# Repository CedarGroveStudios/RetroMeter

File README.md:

# RetroMeter
A breakout and FeatherWing PCB family with CircuitPython code that converts a +/-10V CV signal to a current level compatible with a retro analog ammeter. USB or 3 to 6V battery powered (no internal battery charger). From the collaborative project with John Park’s Workshop.

The Retro CV Meter breakout and FeatherWing board accepts a -10 to +10 volt signal and through an analog op-amp, translates it into a +3.3 to 0 volt signal connected to the Adafruit Trinket M0 or Feather's A1 analog input pin. The A0~ DAC output pin provides current output through a 2K-ohm resistor to the analog meter connection. The maximum DAC value (65535) produces 1.5mA to the attached meter.

The CircuitPython code reads the input voltage and adjusts the DAC output for the scale for the meter. The ``inertia_move`` helper integrates the incoming signal then sends the scaled and smoothed voltage to the on-board meter resistor to convert the voltage to current compabile with the analog meter. The integration routine protects the meter movement from sudden voltage changes.

The most recent version of the code reads a meter scale input from a potentiometer attached to pin A2. The D3 pin provides a PWM output proportional to the absolute value of the input voltage within the specified range.

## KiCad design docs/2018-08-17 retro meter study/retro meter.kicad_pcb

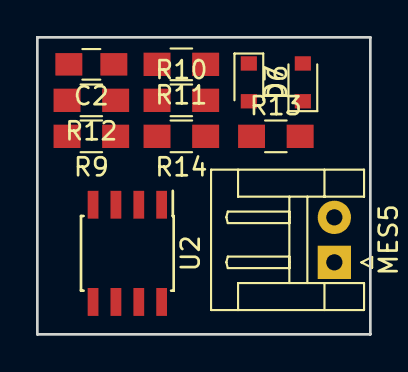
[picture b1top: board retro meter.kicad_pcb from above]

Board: 2 copper layers, 18.5 x 16.5 mm, 11 parts (0 on the bottom side), 7 nets, no tracks yet.

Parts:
C2: 0.1uF; C_0805_HandSoldering
D6, D7: DIODE; D_0805
MES5: 100uA; JST_EH_S02B-EH_02x2.50mm_Angled
R9: 600K; R_0805_HandSoldering
R10, R11, R12: 100K; R_0805_HandSoldering
R13: 33K; R_0805_HandSoldering
R14: 10K; R_0805_HandSoldering
U2: TL072; SOIC-8_3.9x4.9mm_Pitch1.27mm

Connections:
+3V3: D6.1, R10.2
GND: D7.2, MES5.1, R11.1
unnamed: C2.1, R12.1, R14.2, U2.1
unnamed: C2.2, R9.1, R12.2, U2.2
unnamed: MES5.2, R13.1
unnamed: R10.1, R11.2, U2.3
Trinket_A0: D6.2, D7.1, R14.1

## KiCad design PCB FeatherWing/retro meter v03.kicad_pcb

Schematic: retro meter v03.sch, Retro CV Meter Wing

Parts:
C1: 10uF; C_0805
C2: 0.1uF; C_0805
C3: 0.01uF; C_0805
D1: GRN LED; LED_0805_HandSoldering
J1: CV_INPUT; Pin_Header_Straight_1x02_Pitch2.54mm
J2: POWER_SWITCH; Pin_Header_Straight_1x02_Pitch2.54mm
J3: RANGE_SEL; Pin_Header_Straight_1x03_Pitch2.54mm
J4: METER_OUTPUT; Pin_Header_Straight_1x02_Pitch2.54mm
J5: LED1; Pin_Header_Straight_1x02_Pitch2.54mm
J6: LED2; Pin_Header_Straight_1x02_Pitch2.54mm
J7: LED3; Pin_Header_Straight_1x02_Pitch2.54mm
M1: Feather_M4_Express; Adafruit_Feather_M4_Express_bare
MES1: 1.6mA
P1: PKMCS0909E4000-R1
R1: 133K; R_0805
R2, R3, R5, R14, R15: 100K; R_0805
R4: 600K; R_0805
R6, R7: 10K; R_0805
R8: 2K; R_0805_HandSoldering
R9, R10, R11: 220; R_0805_HandSoldering
R12: 100M; R_Axial_DIN0309_L9.0mm_D3.2mm_P2.54mm_Vertical
R13: 470; R_0805
RV1: RANGE_SELECT
U1: TLV2462; SOIC-8_3.9x4.9mm_Pitch1.27mm
U2, U3, U4: 74HCT1G125; TSOP-5_1.65x3.05mm_Pitch0.95mm_hand_solder

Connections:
+3V3: C1.1, C2.1, J3.2, M1.2, R1.2, R13.2, R14.2, U1.8 (V+), U2.6, U3.6, U4.6
/-EN: J2.1, M1.18
/A0~~: M1.5, R8.2, R12.2
/A2: M1.7, R7.1, U1.7
/A3: J3.1, M1.8
/D5: M1.26, U2.2
/D6: M1.25, U3.2
/D9: M1.24, U4.2
/D10: M1.23, P1.1
/Vref1: R1.1, R2.2, U1.3 (+)
/Vref2: R14.1, R15.2, U1.5 (+)
GND: C1.2, C2.2, D1.1, J1.2, J2.2, J3.3, J4.2, J5.2, J6.2, J7.2, M1.4, P1.2, R2.1, R3.1, R15.1, U1.4 (V-), U2.1, U2.3, U3.1, U3.3, U4.1, U4.3
unnamed: C3.1, R5.1, R6.2, U1.1
unnamed: C3.2, R4.1, R5.2, U1.2 (-)
unnamed: D1.2, R13.1
unnamed: J1.1, R3.2, R4.2
unnamed: J4.1, R8.1, R12.1
unnamed: J5.1, R9.1
unnamed: J6.1, R10.1
unnamed: J7.1, R11.1
unnamed: R6.1, R7.2, U1.6 (-)
unnamed: R9.2, U2.4
unnamed: R10.2, U3.4
unnamed: R11.2, U4.4

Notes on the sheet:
Meter output scaling: Adjust R8 for meter full-scale value R8 = 3.3V / 1.5mA = 2.2K ohms
voltage sum stage CV gain = -0.1667 Vref gain = +1.1667
-10V to +10V
+1.416V
input -> output -10v 0v 0v +1.65v +10v +3.3v
power management
microcontroller
desired CV Gain = Voutpk_pk / Vinpk_pk desired CV Gain = 3.3v / 20v = 0.165 actual CV Gain = R5 / R4 = 0.1667 Vref1 = ( 3.3v / 2 ) / [ 1+ ( 100K / 600K ) ] Vref1 = 1.65v / 1.1667 Vref1 = 1.414v Actual Vref1 = [ 3.3v / ( 100K + 133K ) ] * 100K Actual Vref1 = 1.416v C1 = rate / ( 2pi * R5) 0.01uF = 0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
1.0 gain inverter stage
Standalone Analog Mode: Provide power to 3V pin using https://www.adafruit.com/product/2745 Jumper pin A0 to pin A2
(through-hole)
Vf=2.1v @ 5mA
Vf=2.1v @ 10mA
Feather Pin Usage: 3V: powers all internal components and external LEDs GND: common ground for everything A0~: digital-to-analog (DAC) output to series meter resistor A2: analog input from op-amp input signal processing stage A3: analog input from range selection potentiometer D5: digital output to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
range select input
piezo speaker
buffered LED outputs
analog input signal processing stage
+1.650V

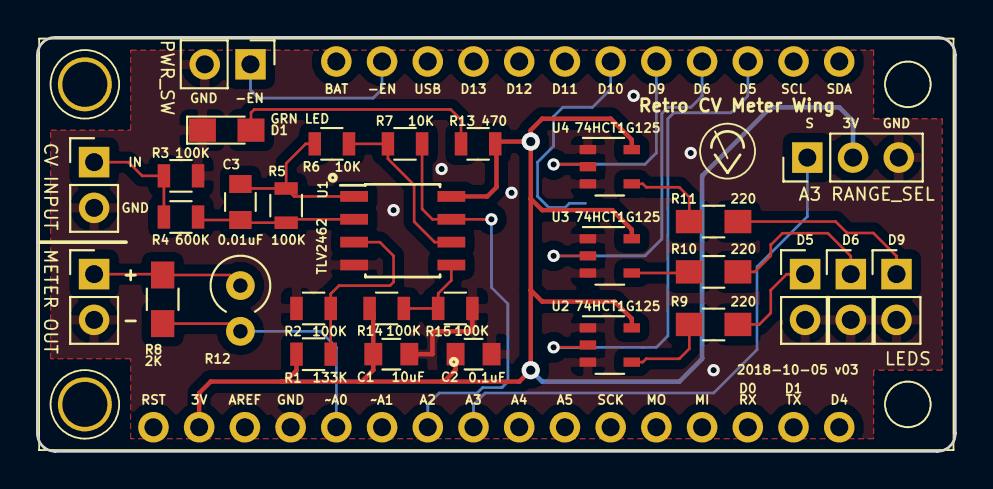
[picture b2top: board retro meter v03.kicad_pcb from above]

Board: 2 copper layers, 51.0 x 23.0 mm, 32 parts (1 on the bottom side), 24 nets.

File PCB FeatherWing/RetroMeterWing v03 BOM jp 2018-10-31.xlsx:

| Retro CV Meter Wing v03
 |  | Designation | Qty | JP Care Pkg | Value | Description | DigiKey | Adafruit
 |  | C1 | 1 |  | 10uF | SMT 0805 capacitor, ceramic, 16v | 490-5519-1-ND‎
 |  | C2 | 1 |  | 0.1uF | SMT 0805 capacitor, ceramic, 16v | 399-11163-1‎
 |  | C3 | 1 | 2 | 0.01uF | SMT 0805 capacitor, ceramic, 16v | 311-3161-1-ND
 |  | D1 | 1 | 2 | Green | SMT 0805 LED, GRN | 754-1651-1-ND
 |  | J1-J7 |  |  |  | Various male pin headers, 0.1" spacing |  | PID #392
 |  | M1 |  |  |  | Feather male pin or socket headers, 0.1" spacing
 |  | P1 | 1 | 2 | PKMCS0909E4000-1 | SMT piezo speaker | 490-9647-1-ND
 |  | R1 | 1 |  | 133K ohms | SMT 0805 resistor 0.1%, 1/8W | YAG1777CT-ND
 |  | R2, R3, R5, R14, R15 | 5 |  | 100K ohms | SMT 0805 resistor, 1% 1/8W | P100KCCT-ND‎
 |  | R5 | 1 |  | 600K ohms (604K) | SMT 0805 resistor, 1% 1/8W | P604KCCT-ND
 |  | R6, R7 | 2 |  | 10K ohms | SMT 0805 resistor, 1% 1/8W | P10.0KCCT-ND‎
 |  | R8 (or R12) | 1 |  | 2K ohms (matched to meter) | SMT 0805 resistor, 1% 1/8W (or through-hole) | YAG1322CT-ND
 |  | R9, R10, R11 | 3 | 6 | 220 ohms | SMT 0805 resistor, 1% 1/8W | YAG3711CT-ND
 |  | R13 | 1 | 2 | 470 ohms | SMT 0805 resistor, 1% 1/8W | YAG3733CT-ND
 |  | RV1 | 1 |  | 10K ohms | Potentiometer
 |  | U1 | 1 | 2 | TLV2462 | Dual SOIC-8 op-amp, single supply 2v to 6v | 296-2434-1-ND
 |  | U2, U3, U4 | 3 | 6 | 74HCT1G125 | SMT TSOP-5 tri-state buffer | ‎1727-6054-1-ND‎

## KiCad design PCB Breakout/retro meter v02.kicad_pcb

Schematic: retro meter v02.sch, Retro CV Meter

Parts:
C1, C3: 0.1uF; C_0805_HandSoldering
C2: 10uF
J1: CV_INPUT; Pin_Header_Straight_1x02_Pitch2.54mm
J2: POWER_SWITCH; Pin_Header_Straight_1x02_Pitch2.54mm
J3: LIPO_BATTERY; JST_PH_S2B-PH-SM4-TB_02x2.00mm_Angled
J4: D0/A2; Pin_Header_Straight_1x03_Pitch2.54mm
J5: D3/A3; Pin_Header_Straight_1x03_Pitch2.54mm
J6: D4/A4; Pin_Header_Straight_1x03_Pitch2.54mm
J7: METER_OUTPUT; Pin_Header_Straight_1x02_Pitch2.54mm
MES1: 1.6mA
R2, R4, R6, R8: 100K; R_0805_HandSoldering
R3: 133K; R_0805_HandSoldering
R5: 600K; R_0805_HandSoldering
R9: 2K; R_0805_HandSoldering
U1: TLV2461; SOIC-8_3.9x4.9mm_Pitch1.27mm
U2: Trinket_M0; Trinket_M0_no_holes

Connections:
+3V3: C2.1, C3.1, J4.2, J5.2, J6.2, R3.2, R8.2, U1.7 (V+), U2.6
+BATT: J2.1, U2.1
/A0~~: R9.2, U2.8
/A1: C1.1, R6.1, U1.6, U2.7
/D0: J4.1, U2.9
/D3: J5.1, U2.4
/D4: J6.1, U2.3
/Vref: R3.1, R4.2, U1.3 (+)
GND: C2.2, C3.2, J1.2, J3.2, J4.3, J5.3, J6.3, J7.2, R2.1, R4.1, U1.4 (V-), U2.2
unnamed: C1.2, R5.1, R6.2, U1.2 (-)
unnamed: J1.1, R2.2, R5.2
unnamed: J2.2, J3.1
unnamed: J7.1, R9.1
unnamed: R8.1, U2.5

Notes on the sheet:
adjust R8 for meter full-scale value R8 = 3.3V / 1.6mA = 2K ohms
0.167 gain inverter stage
Span: adjust R6 Zero: adjust ratio of R3 and R4
C1 = rate / ( 2pi * R5) 0.1uF = 0.038sec / (6.28 * 60K)
-10V to +10V
+1.42V
input -> output -10v +3.3v 0v +1.65v +10v 0v
DAC output scaling
GPIO
power management
microcontroller
Vref = Rf ( Vinpk_pk / ( 2 ( Rf + Rin ) ) ) Vref = 10K ( 20v / ( 2 (10K + 60K ) ) ) Vref = 1.42v
Gain = Voutpk_pk / Vinpk_pk Gain = 3.3v / 20v = 0.165

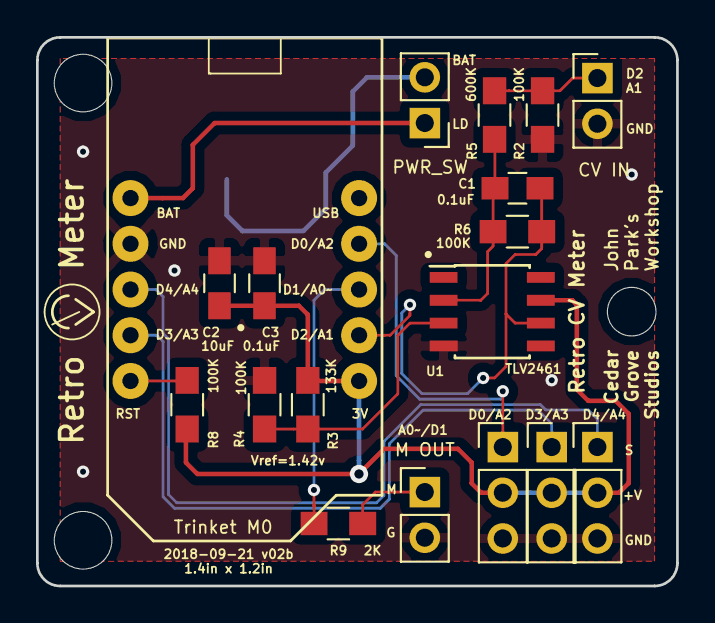
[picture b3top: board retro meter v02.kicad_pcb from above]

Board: 2 copper layers, 35.6 x 30.5 mm, 19 parts (1 on the bottom side), 14 nets.

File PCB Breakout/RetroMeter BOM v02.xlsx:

| Retro CV Meter
 |  | Designation | Qty | Value | Description | DigiKey | Adafruit
 |  | R5 | 1 | 600K ohms (604K) | SMT 0805 resistor, 1% 1/8W | 311-604KCRCT-ND‎
 |  | R2, R4, R6, R8 | 4 | 100K ohms | SMT 0805 resistor, 1% 1/8W | P100KCCT-ND‎
 |  | R3 | 1 | 133K ohms | SMT 0805 resistor, 1% 1/8W | P133KCCT-ND‎
 |  | R9 | 1 | 2K ohms (matched to meter) | SMT 0805 resistor, 1% 1/8W | YAG1322CT-ND
 |  | C1, C3 | 2 | 0.1uF | SMT 0805 capacitor, ceramic, 16v | 399-11163-1‎
 |  | C2 | 1 | 10uF | SMT 0805 capacitor, ceramic, 16v | 490-5519-1-ND‎
 |  | U1 | 1 | TLV2461 | SOIC-8 op-amp, single supply 2v to 6v | 296-2434-1-ND‎
 |  | U2 | 1 | Trinket M0 | microcontroller sub-module | 1528-2361-ND‎ | PID #3500
 |  | J3 | 1 | JST_PH_S2B-PH-SM4-TB_02x2.00mm_Angled | 2-pin SMD JST connector |  | PID #1769
 |  | J1-J7 |  |  | Male pin headers, 0.1" spacing |  | PID #392

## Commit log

2018-08-21 jst connector
    added battery jst connector
2018-09-01 Initial code
2018-09-01 Added external LED support
    Polarity indicators added to GPIO pins. D0=1 when signal is negative, D2=1 when signal is near zero, D4=1 when signal is positive.
2018-09-04 updated
    More fully annotated. Changed default parameters. Improved (slowed) initial meter needle positioning.
2018-09-04 no frills version
    A no frills version of the code without signal integration.
2018-09-04 update default parameters
    changed initial parameters to JP's experimental default values
2018-09-10 selectable scales version
    Reads the 0 to 3.3volt value on pin A2 to select and apply one of six ranges: +/-10v, +/-8v, +/-5v, 0/5v, 0/8v, 0/10v
2018-09-10 meter scale selection via analog input A2
    updated to include scale selection via analog input A2
    moved negative signal level LED from D0 to D3
2018-09-17 amber led version
    amber led attached to D3
2018-09-21 added feather wing files
2018-09-30 updated meter scale control
    Added hysteresis to the scale control potentiometer input. Changes to the scale flash the amber LED on D3.
2018-10-02 analog meter tester utilizing the Retro CV Meter PCB
    The Meter Tester measures and displays analog meter parameters. The meter voltage is monitored by a probe connection from analog input A4. Up to +1.65mA current is output from the Retro CV Meter boar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
2018-10-03 analog meter tester utilizing Retro CV Meter PCB
    The Meter Tester measures and displays analog meter parameters. The meter voltage is monitored by a probe connection from analog input A4. Up to +1.65mA current is output from the Retro CV Meter boar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
2018-10-14 updated for revised PCB
2018-10-17 pinout diagrams
2018-10-17 updated pinout diagram
2018-10-18 updated pinout graphics
2018-10-27 modification for meter tester scheme
2018-10-27 meter tester diagram
2018-10-28 fritzing diagram
2019-04-25 Create LICENSE
2019-04-30 Meter Fundamentals Guide
2019-09-04 include alternate board designs
2019-09-05 remove rev 2a bodge graphics
2021-07-12 update documentation
